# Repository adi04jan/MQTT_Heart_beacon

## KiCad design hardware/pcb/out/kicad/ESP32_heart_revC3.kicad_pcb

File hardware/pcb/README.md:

# Heart Beacon carrier rev C3

One single-sided board, 48 x 37 mm (rev B: 38.1 x 64.4), made to hide behind the 45 x 35 mm cell so the heart can
be 91 mm wide. Rev B's parts and nets with a new GPIO map and narrow socket pads. No jumpers.

```
../cage/.venv/Scripts/python revc.py place     # placement preview -> out/revC3_place.png
../cage/.venv/Scripts/python revc.py --own     # place, route, write the EAGLE files, convert to KiCad, fill, DRC (~10 s)
```

Outputs, next to the rev B files in the EAGLE project folder (nothing else there is touched):
`ESP32_heart_revC3.sch`, `ESP32_heart_revC3_build.scr`, `ESP32_heart_revC3_rules.dru`.
Here: `out/revC3_copper_side.png`, `out/revC3_from_the_back.png`, `out/kicad/ESP32_heart_revC3.kicad_pcb`, `out/kicad/drc.json`.

## In EAGLE

1. Open `ESP32_heart_revC3.sch` (there must be no `ESP32_heart_revC3.brd` yet).
2. File > Execute Script > `ESP32_heart_revC3_build.scr`. It runs `BOARD` (answer yes to "create from schematic"),
   deletes EAGLE's default outline, draws the outline (layers 20, 46, 22), moves and rotates every part, draws every
   track on layer 1, the VSYS wire pad, the GND polygon, and ends with `RATSNEST`.
3. In the board editor: DRC > Load `ESP32_heart_revC3_rules.dru`, then Check.
4. `RATSNEST` should report nothing to do. If it shows a GND airwire, the pour came out narrower in EAGLE than in
   KiCad at that spot: draw that one GND track by hand.

The schematic and the script were written by `revc.py` and checked against each other (same nets, same pads) and in
KiCad. They have not been opened in EAGLE.

## GPIO map

| Signal | Net | rev B | rev C3 |
|---|---|---|---|
| Button | A1 | GPIO0 | GPIO0 |
| LIS3DH INT1 | IMU_INT | GPIO1 | GPIO1 |
| LIS3DH SCL | SCL | GPIO9 | **GPIO2** |
| LIS3DH SDA | SDA | GPIO8 | GPIO8 |
| USB sense | USB_CHARGE | GPIO3 | GPIO3 |
| VBAT | VBAT_SENSE | GPIO4 | GPIO4 |
| LED rail enable | LED_EN (rev B: "7") | GPIO7 | **GPIO20** |
| LED data | LED_CTRL | GPIO10 | **GPIO21** |
| tied to GND | GND | GPIO5 | GPIO5 |

Free: GPIO6, 7, 9, 10. GPIO21 is the boot ROM's UART TX: it chatters at reset, but the LED rail is off then
(R8 holds the enable low), so the LEDs do not see it.

## Board

- Copper on EAGLE's Top, which faces the cell. SMD parts on that side. Every through-hole part (module sockets,
  LIS3DH sockets, S1, S3, headers) sits on the other side and is soldered on the copper side.
- Socket and header pads: oblong 1.3 mm along the row x 2.2 mm across, 0.8 mm drill (packages
  `MODULE_ESP32-C3_SUPERMINI_TH`, `MA06-1`, `MA03-1`, `1X02`, edited inside the schematic's libraries; the `.dru` sets
  restring 0.25 mm and long-pad elongation 69 % to match). One 0.4 mm track passes between two pins.
- The LIS3DH's unused pins (J1 5-6, J2 2-3) keep their pads; nothing routes to them.
- `S1` is unmirrored in EAGLE only so that its pin 1 lands top left; it mounts on the back like every other
  through-hole part.
- The VSYS wire pad (2 mm, 1 mm hole, net USB_OUT) is a via element as on rev B. It is at (41.6, 19.65), about
  10 mm from the module's PD1 corner.
- Layer 46 carries the outline cut with four 1.9 mm tabs. No mounting holes: the printed mount clips the board edges.

| Part | Where (copper side view, origin bottom left) |
|---|---|
| U1 SuperMini | top centre, USB-C flush with the top edge on the centre line |
| S1 button | below the module on the centre line |
| S3 slide switch | right edge, slider overhanging by 2.2 mm |
| LIS3DH (SV3, SV5) | left, SV3 next to the module's left pin row |
| USB sense divider | between the LIS3DH pin rows |
| VBAT divider | under the module; R21 between S1's pin rows |
| LED rail (Q5, R8, R7, Q6, R6, R9) | between S1's pin rows |
| SV1 LED header, C7 | bottom left |
| Power path (D2, Q2, C18, R5, JP1) | top right, next to S3 |
| Charger (U3 and passives), BATT header | bottom right |

## Rules and result

- 0.4 mm tracks, 0.35 mm clearance everywhere, 1.0 mm to the board edge, one layer, no jumpers.
- BATT+, USB_IN, VSYS, LED+ and the nets between them are 0.8 mm wherever 0.35 mm still holds, 0.4 mm elsewhere.
- GND: a polygon over the whole board (isolate 0.35, width 0.4, thermals on, orphans off), plus GND tracks where
  the pour alone would be too narrow.
- KiCad DRC at these rules, zone filled: 0 errors, 0 unconnected, 1 warning (the wire pad is a via on one layer).
- Routing: `router.py`, a grid router that places one connection at a time. The order and a handful of reserved
  lanes (`FIRST`, `LAST`, `PRELINKS` in `revc.py`) are what make it close without jumpers; change the placement and
  they may need another look. It can place 1210 jumpers (package `R1210J`, two tracks under one) when a connection
  is walled in; none were needed. Freerouting 2.1.0 can still be run with `revc.py` (without `--own`) but does not
  stop or save reliably on this PC.

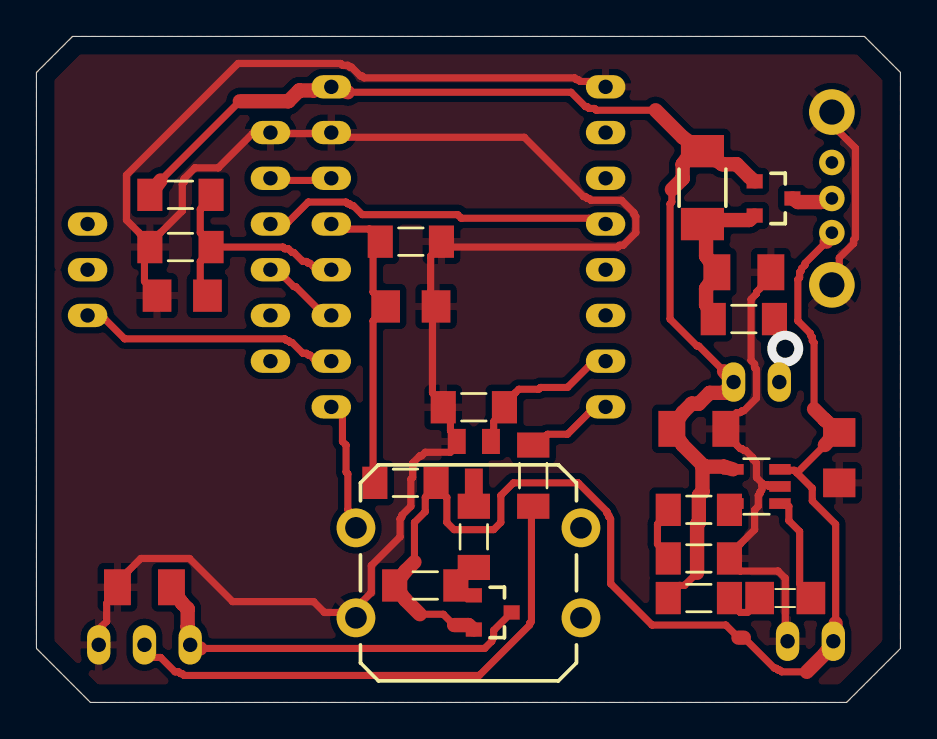
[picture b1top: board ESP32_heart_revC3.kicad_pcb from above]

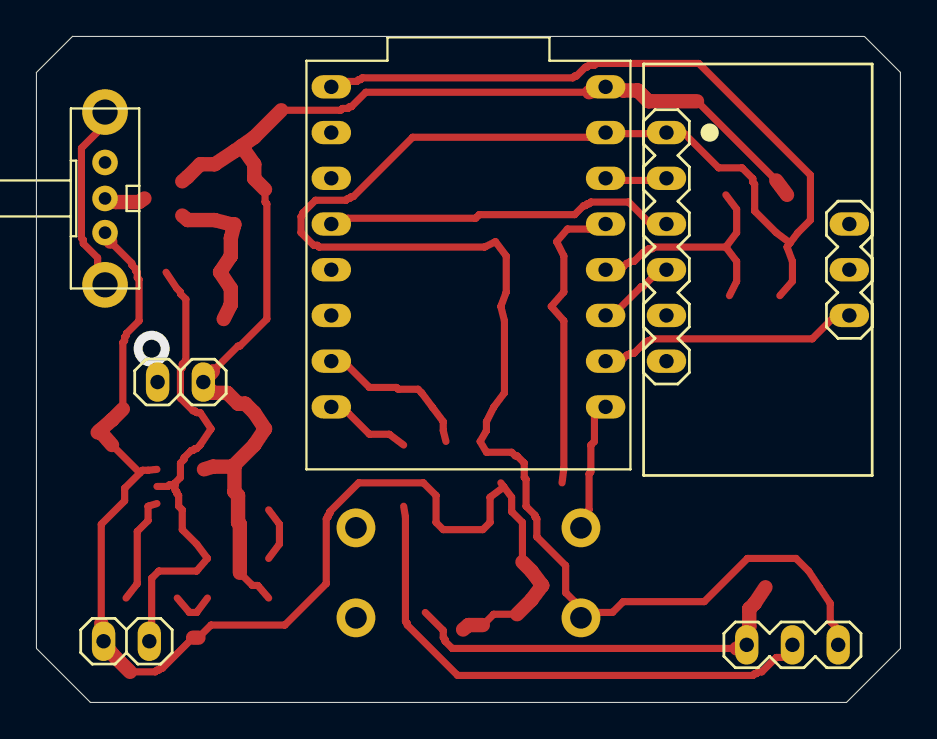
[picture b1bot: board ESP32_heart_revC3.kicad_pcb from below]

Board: 2 copper layers, 48.0 x 37.0 mm, 32 parts (7 on the bottom side), 23 nets.

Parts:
BATT: 1X02
C2, C32: 100nf; C1206
C6: 1uf; C1206
C7, C17, C18: 100nf; C1206K
D2: DO-214AC
JP1: 1X02
LED1: DNP; 1206
Q2, Q6: CMN3401M; SOT23-3
Q5: CMN2302BSM; SOT23
R1: 68k; M1406
R2, R3, R4, R7: 1K; M1406
R5: 0; M1406
R6, R8: 10K; M1406
R9: 330; M1406
R14: 100k; M1406
R21, R22: 1M; M1406
S1: SWITCH-MOMENTARY-2-CLOSED; TACTILE-PTH-12MM
S3: EG1213
SV1, SV5: MA03-1
SV3: MA06-1
U1: ESP32-C3_SUPERMINI_TH; MODULE_ESP32-C3_SUPERMINI_TH
U3: TP4054

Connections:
3V3: SV3.2, U1.3.3
A1: S1.1, U1.0
BATT+: BATT.1, C6.1, Q6.2, R6.2, R21.2, S3.3, U3.3
GND: BATT.2, C2.2, C6.2, C7.2, C17.2, C18.2, C32.2, Q5.2, R4.2, R8.1, R14.1, R22.1, S1.3, S3.MT1, S3.MT2, SV1.3, SV3.1, U1.5, U1.G, U3.2
IMU_INT: SV5.1, U1.1
LED_CTRL: R9.1, U1.21
LED_DIN: R9.2, SV1.2
LED_EN: Q5.1, R8.2, U1.20
unnamed: R3.2, U3.5
unnamed: R3.1, R4.1
unnamed: LED1.C, U3.1
unnamed: LED1.A, R2.1
unnamed: Q2.3, S3.2
unnamed: Q5.3, R7.1
unnamed: Q6.1, R6.1, R7.2
unnamed: C7.1, Q6.3, SV1.1
unnamed: C18.1, D2.C, Q2.2, R5.2
SCL: SV3.4, U1.2
SDA: SV3.3, U1.8
USB_CHARGE: C32.1, R1.1, R14.2, U1.3
USB_IN: C17.1, D2.A, JP1.1, Q2.1, R1.2, R2.2, U1.5V, U3.4
USB_OUT: JP1.2, R5.1
VBAT_SENSE: C2.1, R21.1, R22.2, U1.4

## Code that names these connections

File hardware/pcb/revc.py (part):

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POWER, POWER_WIDE = 0.55, 0.8              # power nets are routed at 0.55 and widened to 0.8 wherever 0.35 still holds
POWER_NETS = {"BATT+", "USB_IN", "USB_OUT", "N$15", "N$18", "N$6"}   # cell, USB, VSYS, LED+, and the path between them
JUMPER_PKG = dict(name="R1210J", pad=(1.0, 2.6), pitch=3.0)   # 1210 on narrow pads: 2.0 mm between them = two tracks
LANDING = ("USB_OUT", 41.6, 19.65)          # 2 mm pad for the module's VSYS (PD1) wire, next to that corner as on rev B
LANDING_D = 2.0

# GPIO map: net -> module pad. The firmware's pin map is per-board Kconfig, so signals sit where they route best.
PINMAP = {"A1": "0", "IMU_INT": "1", "SCL": "2", "SDA": "8", "VBAT_SENSE": "4", "USB_CHARGE": "3",
          "LED_EN": "20", "LED_CTRL": "21"}
FIRST = ("N$18", "USB_IN")                              # nets the completion router takes before the rest
LAST = ("BATT+", "GND")                    # GND is a pour: it takes what is left
PRELINKS = [("GND", ("S3", "MT1"), ("S3", "MT2")), ("GND", ("C18", "2"), ("C17", "2")), ("BATT+", ("S3", "3"), ("C6", "1")), ("BATT+", ("R21", "2"), ("R6", "2")), ("BATT+", ("R6", "2"), ("Q6", "2")),
            ("LED_DIN", ("R9", "2"), ("SV1", "2")), ("N$15", ("Q6", "3"), ("SV1", "1"))]
RENAME = {"7": "LED_EN"}                   # rev B called the LED enable net "7" after its pin
# Socket and header pads: oblong, 1.3 mm along the row, 2.2 mm across, 0.8 mm drill: one 0.4 mm track fits between pins
NARROW = {"MODULE_ESP32-C3_SUPERMINI_TH": "R0", "MA06-1": "R90", "MA03-1": "R90", "1X02": "R90"}
NPAD, NDRILL, ELONG = 1.3, 0.8, 2.2 / 1.3
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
